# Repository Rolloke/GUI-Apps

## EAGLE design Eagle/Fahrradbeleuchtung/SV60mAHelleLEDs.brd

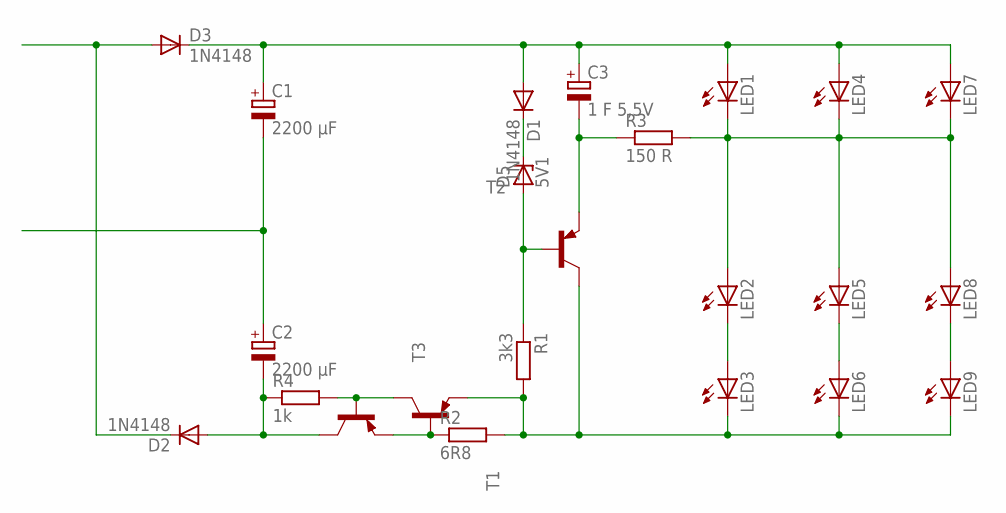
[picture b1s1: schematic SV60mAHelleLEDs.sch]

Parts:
C1, C2: 2200 µF; E5-10,5
C3: 1 F 5,5V; E3,5-10
D1, D2, D3: 1N4148; DO35-10
D5: 5V1; SOD81
LED1, LED2, LED3, LED4, LED5, LED6, LED7, LED8, LED9: LED5MM
R1: 3k3; 0207/10
R2: 6R8; 0207/10
R3: 150 R; 0207/10
R4: 1k; 0207/10
T1, T2, T3: 2N2907-PNP-TO18-EBC; TO18

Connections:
D1: D2.C, D3.A
D2: C1.-, C2.+
LV2: LED3.K (C), LED6.K (C), LED9.K (C), R1.2, R2.2, T1.1 (E), T2.3 (C)
unnamed: C1.+, C3.+, D1.A, D3.C, LED1.A, LED4.A, LED7.A
unnamed: C2.-, D2.A, R4.1, T3.3 (C)
unnamed: R2.1, T1.2 (B), T3.1 (E)
unnamed: R4.2, T1.3 (C), T3.2 (B)
unnamed: D5.A, R1.1, T2.2 (B)
unnamed: D1.C, D5.C
unnamed: C3.-, R3.1, T2.1 (E)
unnamed: LED5.K (C), LED6.A
unnamed: LED1.K (C), LED2.A, LED4.K (C), LED5.A, LED7.K (C), LED8.A, R3.2
unnamed: LED2.K (C), LED3.A
unnamed: LED8.K (C), LED9.A

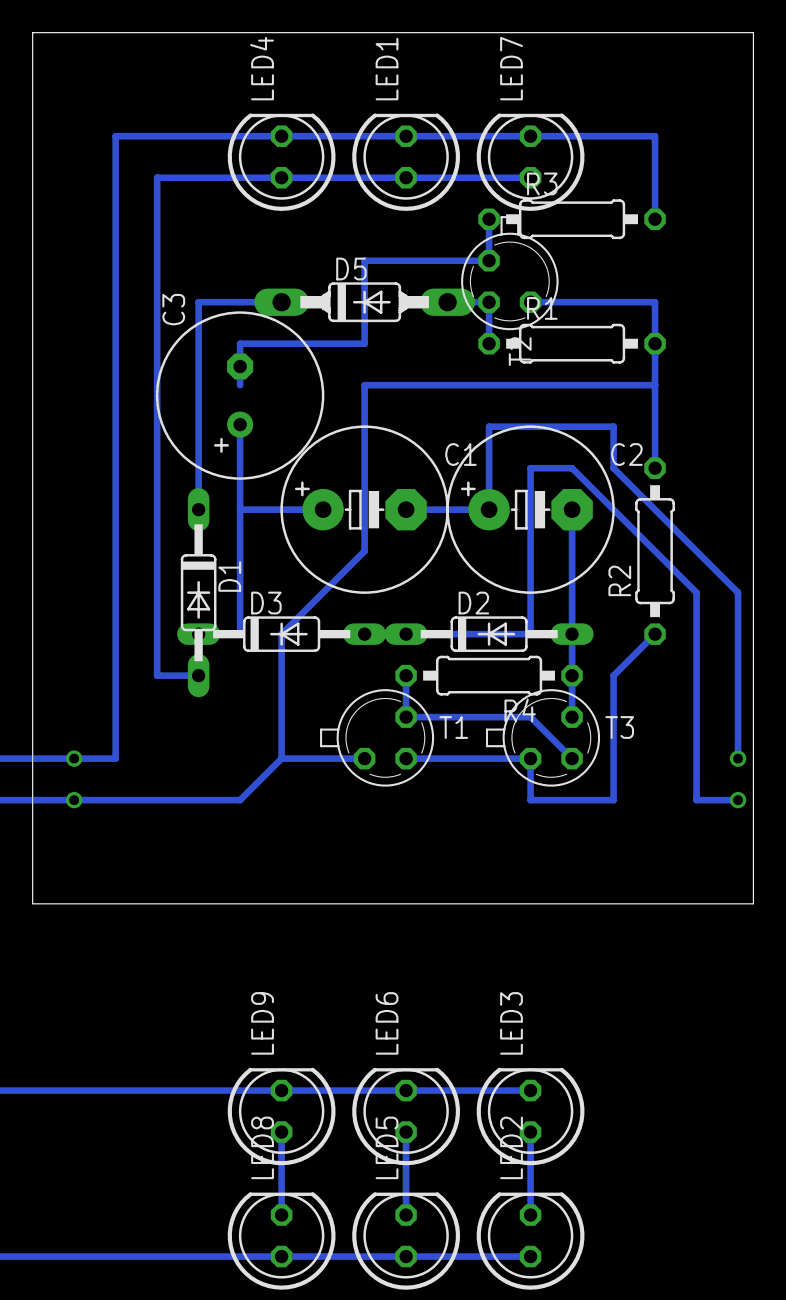
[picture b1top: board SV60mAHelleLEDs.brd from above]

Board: 2 copper layers, 44.1 x 53.3 mm, 23 parts (0 on the bottom side), 14 nets.

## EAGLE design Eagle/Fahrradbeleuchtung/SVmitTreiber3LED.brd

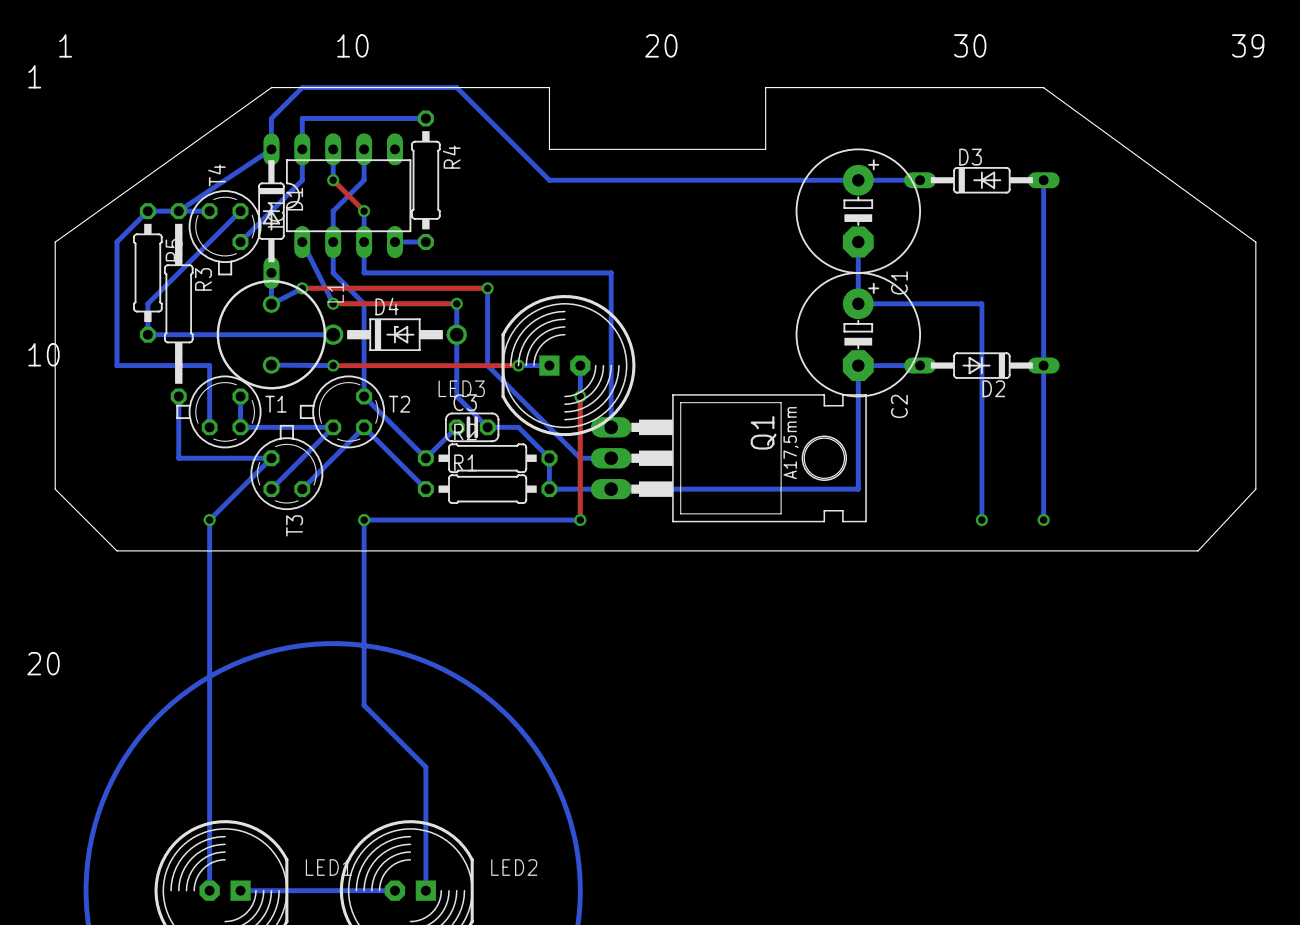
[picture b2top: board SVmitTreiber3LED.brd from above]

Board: 2 copper layers, 98.7 x 38.1 mm, 22 parts (0 on the bottom side), 16 nets.

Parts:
C1, C2: 2200 µF; E5-10,5
C3: C025-024X044
D1: 1N4446; DO35-10
D2, D3: 1N4148; DO35-10
D4: 15 V 1W; DO41Z10
IC1: NE555; DIL-08
L1: 6000-XXXX-RC
LED1, LED2, LED3: LED10MM
Q1: BUZ11; TO220
R1, R4: 100k; 0207/10
R2, R5: 3k9; 0207/10
R3: 0R2; 0207/15
T1, T2, T3, T4: 2N2907; TO18

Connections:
D1: D2.C, D3.A
D2: C1.-, C2.+
LV1: LED1.K, LED2.A
LV2: C2.-, C3.2, D2.A, D4.A, IC1.1, Q1.3, R1.2, R2.2
unnamed: C1.+, D1.C, D3.C, R3.1, R5.1, T1.1, T4.3
unnamed: T1.2, T1.3, T2.1, T3.2
unnamed: R1.1, T2.2, T3.3
unnamed: C3.1, IC1.2, IC1.6, R2.1, T2.3
unnamed: IC1.3, IC1.7, Q1.1
unnamed: IC1.4, R4.2
unnamed: D1.A, L1.1, Q1.2
unnamed: LED1.A, R3.2, T3.1
unnamed: D4.C, R5.2, T4.2
unnamed: LED2.K, LED3.A
unnamed: IC1.8, R4.1, T4.1
SW2LV: L1.2, LED3.K

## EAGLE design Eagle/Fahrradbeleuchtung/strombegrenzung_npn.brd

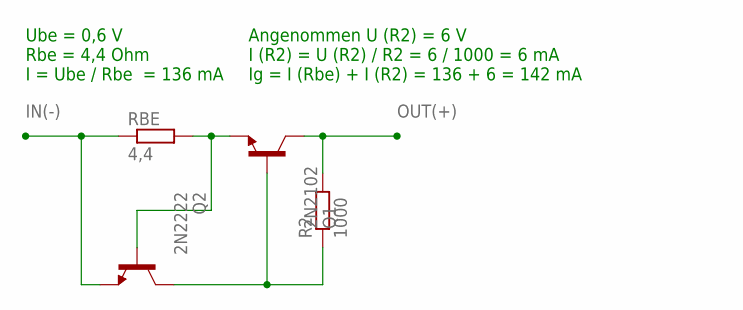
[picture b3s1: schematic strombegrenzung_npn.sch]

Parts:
Q1: 2N2102; TO5
Q2: 2N2222; TO18
R2: 1000; 0207/10
RBE: 4,4; 0207/7

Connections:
IN(-): Q2.1 (E), RBE.1
unnamed: Q1.1 (E), Q2.2 (B), RBE.2
unnamed: Q1.2 (B), Q2.3 (C), R2.1
OUT(+): Q1.3 (C), R2.2

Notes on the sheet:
Ube = 0,6 V Rbe = 4,4 Ohm I = Ube / Rbe = 136 mA
Angenommen U (R2) = 6 V I (R2) = U (R2) / R2 = 6 / 1000 = 6 mA Ig = I (Rbe) + I (R2) = 136 + 6 = 142 mA

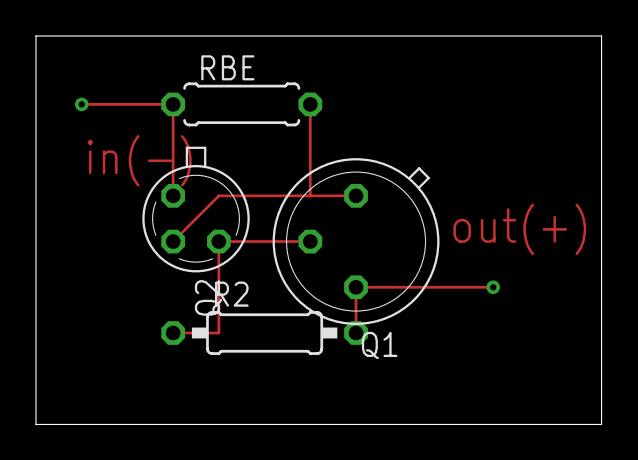
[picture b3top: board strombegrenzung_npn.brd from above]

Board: 2 copper layers, 31.4 x 21.6 mm, 4 parts (0 on the bottom side), 4 nets.
